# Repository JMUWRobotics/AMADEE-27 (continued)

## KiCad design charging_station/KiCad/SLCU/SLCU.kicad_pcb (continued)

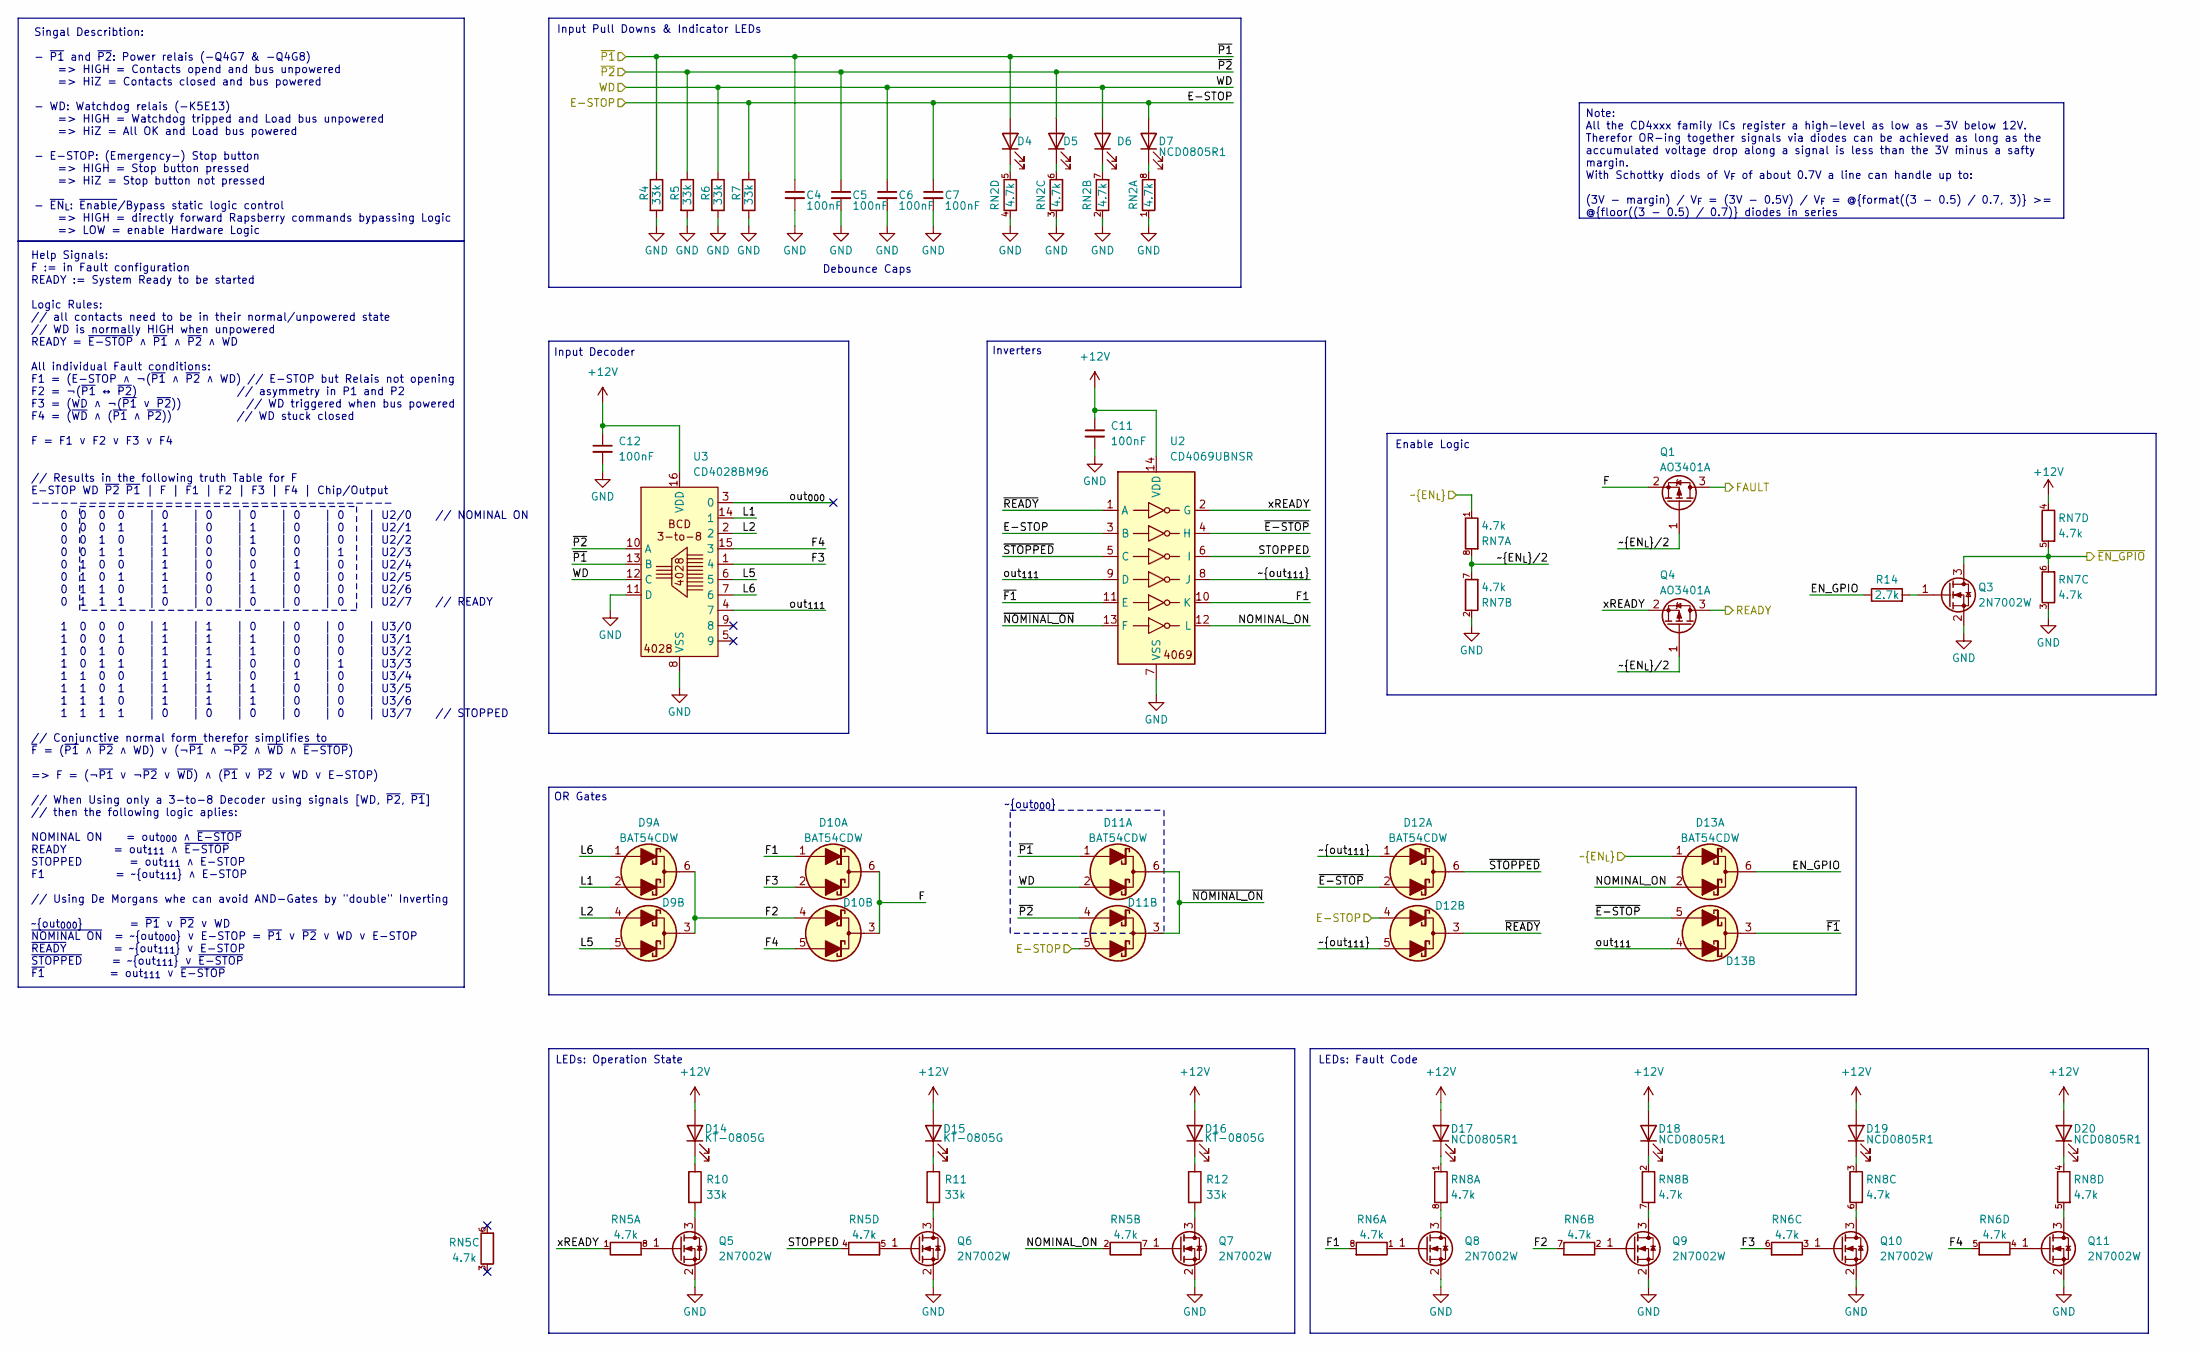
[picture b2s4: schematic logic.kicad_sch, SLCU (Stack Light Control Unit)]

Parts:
C4, C5, C6, C7, C11, C12: 100nF; C_0603_1608Metric
D4, D5, D6, D7, D17, D18, D19, D20: NCD0805R1; LED_0805_2012Metric_Pad1.15x1.40mm_HandSolder; MPN NCD0805R1; LCSC Part C84256
D9, D10, D11, D12, D13: BAT54CDW; SOT-363_SC-70-6
D14, D15, D16: KT-0805G; LED_0805_2012Metric_Pad1.15x1.40mm_HandSolder; MPN KT-0805G; LCSC Part C2297
Q1, Q4: AO3401A; SOT-23; MPN AO3401A; LCSC Part C15127
Q3, Q5, Q6, Q7, Q8, Q9, Q10, Q11: 2N7002W; SOT-323_SC-70; MPN 2N7002W; LCSC Part C7420322
R4, R5, R6, R7, R10, R11, R12: 33k; R_0402_1005Metric; LCSC Part C25779
R14: 2.7k; R_0603_1608Metric; LCSC Part C13167
RN2, RN5, RN6, RN7, RN8: 4.7k; RES-ARRAY-SMD_0603-8P-L3.2-W1.6-BL; MPN 4D03WGJ0472T5E; LCSC Part C1980
U2: CD4069UBNSR; SOIC127P780X200-14N; Mouser Part Number 595-CD4069UBNSR
U3: CD4028BM96; D16-L; MPN CD4028BM96; LCSC Part C131484

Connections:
+12V: C11.1, C12.1, D14.2 (A), D15.2 (A), D16.2 (A), D17.2 (A), D18.2 (A), D19.2 (A), D20.2 (A), RN7.4 (R4.1), U2.14 (VDD), U3.16 (VDD); also elsewhere on the board
/E-STOP: C7.1, D7.2 (A), D11.5 (A2), D12.4 (A2), R7.1, U2.3 (B); also elsewhere on the board
/Logic/EN_GPIO: D13.6 (K1), R14.1
/Logic/F: D10.3 (K2), D10.6 (K1), Q1.2 (S)
/Logic/F1: D10.1 (A1), RN6.8 (R1.2), U2.10 (K)
/Logic/F2: D9.3 (K2), D9.6 (K1), D10.4 (A2), RN6.7 (R2.2)
/Logic/F3: D10.2 (A1), RN6.6 (R3.2), U3.1 (4)
/Logic/F4: D10.5 (A2), RN6.5 (R4.2), U3.15 (3)
/Logic/FAULT: Q1.3 (D); also elsewhere on the board
/Logic/L1: D9.2 (A1), U3.14 (1)
/Logic/L2: D9.4 (A2), U3.2
/Logic/L5: D9.5 (A2), U3.6 (5)
/Logic/L6: D9.1 (A1), U3.7 (6)
/Logic/NOMINAL_ON: D13.2 (A1), RN5.2 (R2.1), U2.12 (L)
/Logic/READY: Q4.3 (D); also elsewhere on the board
/Logic/STOPPED: RN5.4 (R4.1), U2.6 (I)
/Logic/out_{000}: U3.3 (0)
/Logic/out_{111}: D13.4 (A2), U2.9 (D), U3.4 (7)
/Logic/xREADY: Q4.2 (S), RN5.1 (R1.1), U2.2 (G)
/Logic/~E-STOP: D12.2 (A1), D13.5 (A2), U2.4 (H)
/Logic/~EN_GPIO: Q3.3 (D), RN7.5 (R4.2), RN7.6 (R3.2); also elsewhere on the board
/Logic/~EN_{L}/2: Q1.1 (G), Q4.1 (G), RN7.7 (R2.2), RN7.8 (R1.2)
/Logic/~F1: D13.3 (K2), U2.11 (E)
/Logic/~NOMINAL_ON: D11.3 (K2), D11.6 (K1), U2.13 (F)
/Logic/~READY: D12.3 (K2), U2.1 (A)
/Logic/~STOPPED: D12.6 (K1), U2.5 (C)
/Logic/~out_{111}: D12.1 (A1), D12.5 (A2), U2.8 (J)
/WD: C6.1, D6.2 (A), D11.2 (A1), R6.1, U3.12 (C); also elsewhere on the board
/~EN_{L}: D13.1 (A1), RN7.1 (R1.1); also elsewhere on the board
/~P1: C4.1, D4.2 (A), D11.1 (A1), R4.1, U3.13 (B); also elsewhere on the board
/~P2: C5.1, D5.2 (A), D11.4 (A2), R5.1, U3.10 (A); also elsewhere on the board
GND: C4.2, C5.2, C6.2, C7.2, C11.2, C12.2, Q3.2 (S), Q5.2 (S), Q6.2 (S), Q7.2 (S), Q8.2 (S), Q9.2 (S), Q10.2 (S), Q11.2 (S), R4.2, R5.2, R6.2, R7.2, RN2.1 (R1.1), RN2.2 (R2.1), RN2.3 (R3.1), RN2.4 (R4.1), RN7.2 (R2.1), RN7.3 (R3.1), U2.7 (VSS), U3.8 (VSS), U3.11 (D); also elsewhere on the board
unnamed: D4.1 (K), RN2.5 (R4.2)
unnamed: D5.1 (K), RN2.6 (R3.2)
unnamed: D6.1 (K), RN2.7 (R2.2)
unnamed: D7.1 (K), RN2.8 (R1.2)
unnamed: D14.1 (K), R10.1
unnamed: D15.1 (K), R11.1
unnamed: D16.1 (K), R12.1
unnamed: D17.1 (K), RN8.1 (R1.1)
unnamed: D18.1 (K), RN8.2 (R2.1)
unnamed: D19.1 (K), RN8.3 (R3.1)
unnamed: D20.1 (K), RN8.4 (R4.1)
unnamed: Q3.1 (G), R14.2
unnamed: Q5.3 (D), R10.2
unnamed: Q5.1 (G), RN5.8 (R1.2)
unnamed: Q6.3 (D), R11.2
unnamed: Q6.1 (G), RN5.5 (R4.2)
unnamed: Q7.3 (D), R12.2
unnamed: Q7.1 (G), RN5.7 (R2.2)
unnamed: Q8.3 (D), RN8.8 (R1.2)
unnamed: Q8.1 (G), RN6.1 (R1.1)
unnamed: Q9.3 (D), RN8.7 (R2.2)
unnamed: Q9.1 (G), RN6.2 (R2.1)
unnamed: Q10.3 (D), RN8.6 (R3.2)
unnamed: Q10.1 (G), RN6.3 (R3.1)
unnamed: Q11.3 (D), RN8.5 (R4.2)
unnamed: Q11.1 (G), RN6.4 (R4.1)

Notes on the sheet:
Input Decoder
Enable Logic
~{out_{000}}
Help Signals: F := in Fault configuration READY := System Ready to be started Logic Rules: // all contacts need to be in their normal/unpowered state // WD is normally HIGH when unpowered READY = ~{E-STOP} ∧ ~{P1} ∧ ~{P2} ∧ WD All individual Fault conditions: F1 = (E-STOP ∧ ¬(~{P1} ∧ ~{P2} ∧ WD) //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
OR Gates
LEDs: Operation State
Singal Describtion: - ~{P1} and ~{P2}: Power relais (-Q4G7 & -Q4G8) => HIGH = Contacts opend and bus unpowered => HiZ = Contacts closed and bus powered - WD: Watchdog relais (-K5E13) => HIGH = Watchdog tripped and Load bus unpowered => HiZ = All OK and Load bus powered - E-STOP: (Emergency-) Stop b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
Debounce Caps
LEDs: Fault Code
Inverters
Input Pull Downs & Indicator LEDs
Note: All the CD4xxx family ICs register a high-level as low as -3V below 12V. Therefor OR-ing together signals via diodes can be achieved as long as the accumulated voltage drop along a signal is less than the 3V minus a safty margin. With Schottky diods of V_{F} of about 0.7V a line can handle up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

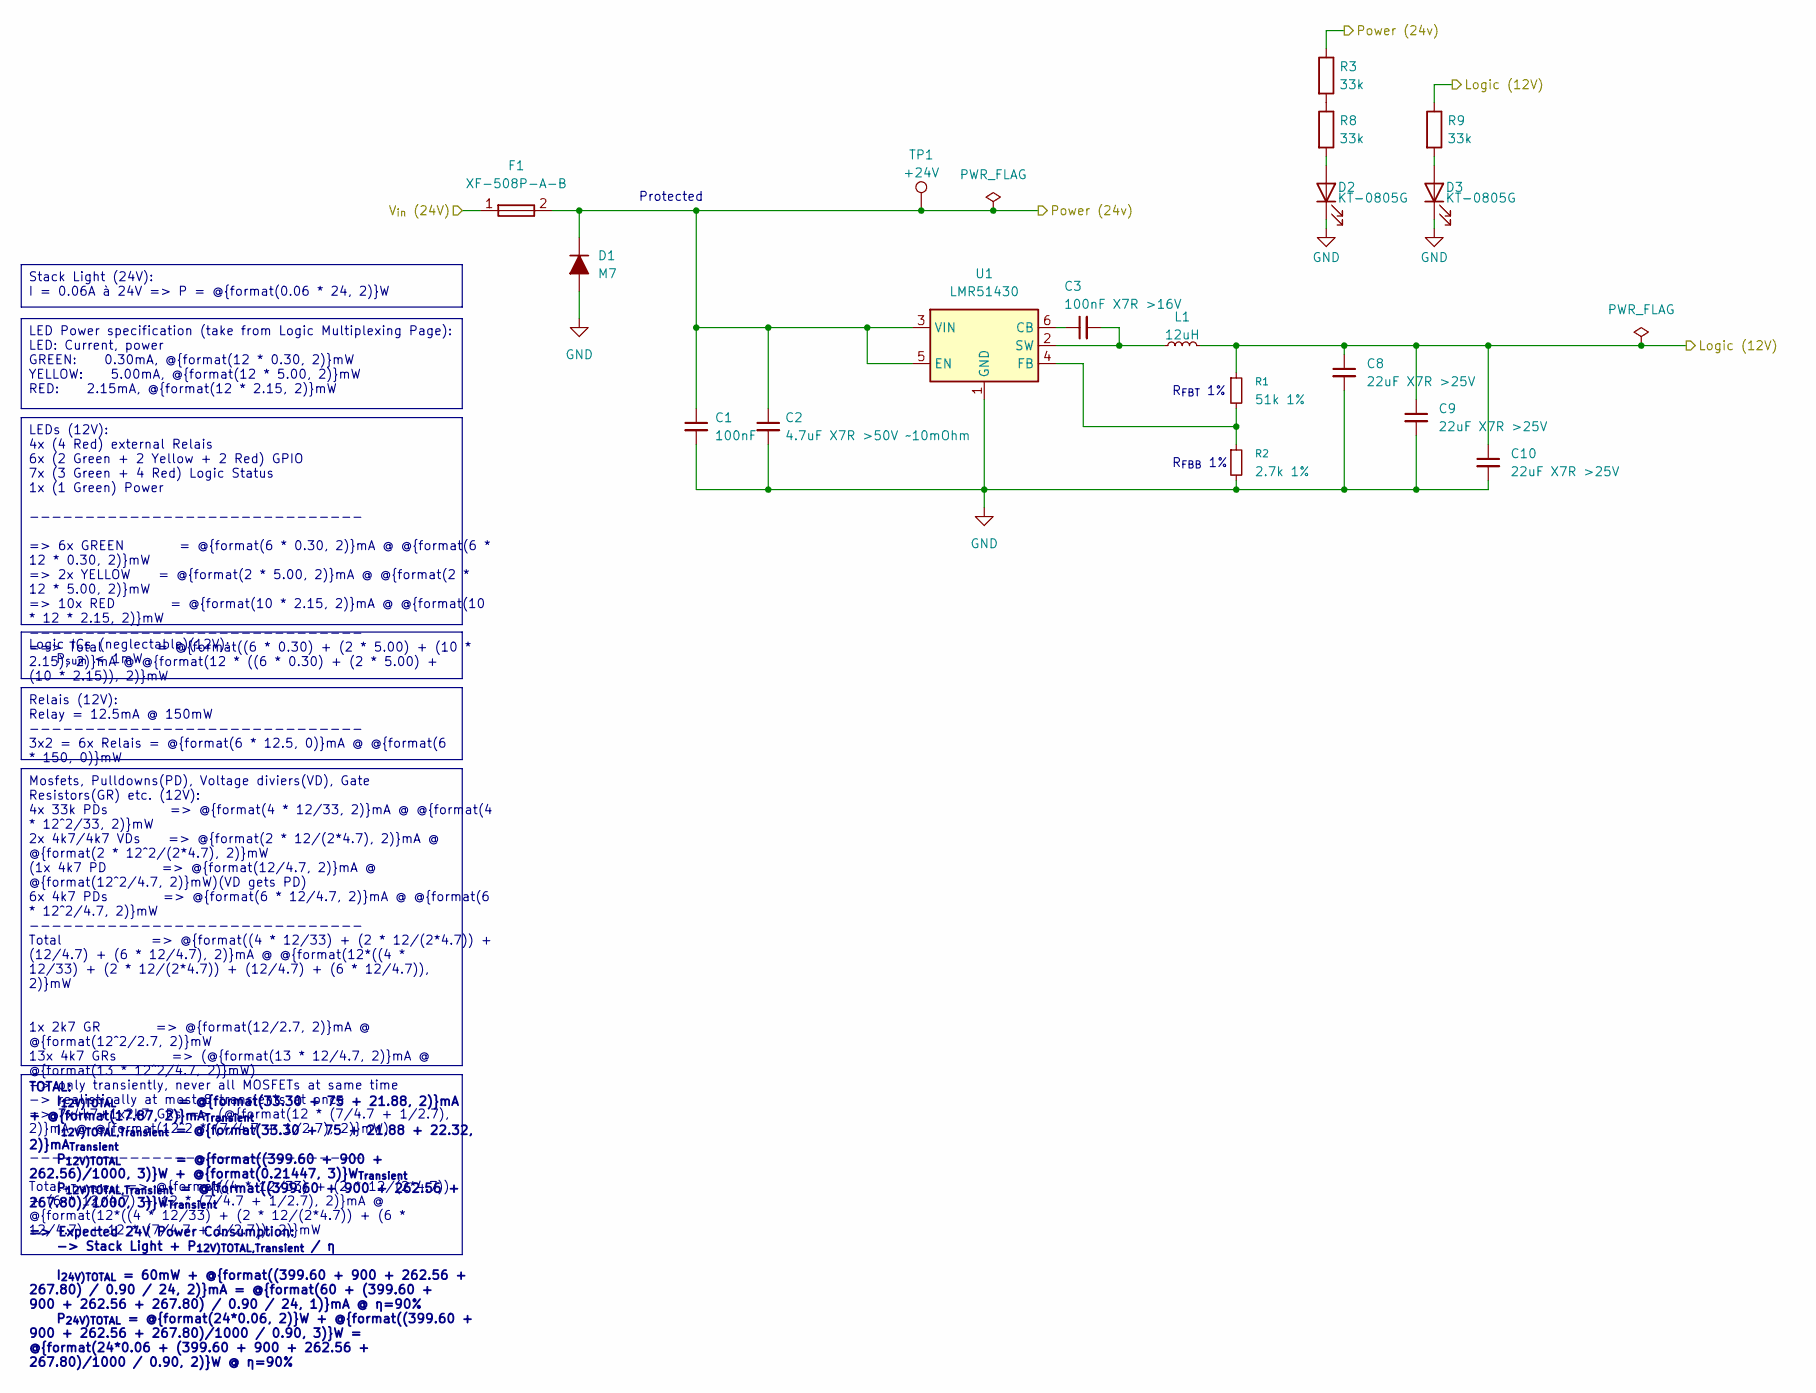
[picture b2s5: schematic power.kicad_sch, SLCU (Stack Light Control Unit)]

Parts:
C1: 100nF; C_0603_1608Metric
C2: 4.7uF X7R >50V ~10mOhm; C_1206_3216Metric
C3: 100nF X7R >16V; C_0603_1608Metric
C8, C9, C10: 22uF X7R >25V; C_0805_2012Metric_Pad1.18x1.45mm_HandSolder
D1: M7; D_SMA
D2, D3: KT-0805G; LED_0805_2012Metric_Pad1.15x1.40mm_HandSolder; MPN KT-0805G; LCSC Part C2297
F1: XF-508P-A-B; FUSE-TH_XF-508P-A-B; MPN XF-508P-A-B; LCSC Part C19727304
L1: 12uH; L_12x12mm_H8mm; MPN CDRH127NP-120MC; LCSC Part C338772
R1: 51k 1%; R_0603_1608Metric; LCSC Part C23196
R2: 2.7k 1%; R_0603_1608Metric; LCSC Part C13167
R3, R8, R9: 33k; R_0402_1005Metric; LCSC Part C25779
TP1: +24V; TestPoint_Pad_D1.5mm
U1: LMR51430; SOT-23-6

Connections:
+12V: C8.1, C9.1, C10.1, L1.2, R1.1, R9.1; also elsewhere on the board
+24V: C1.1, C2.1, D1.1 (K), F1.2, R3.1, TP1.1 (1_1), U1.3 (VIN), U1.5 (EN); also elsewhere on the board
/Power/V_{in} (24V): F1.1; also elsewhere on the board
GND: C1.2, C2.2, C8.2, C9.2, C10.2, D1.2 (A), D2.1 (K), D3.1 (K), R2.2, U1.1 (GND); also elsewhere on the board
unnamed: D2.2 (A), R8.2
unnamed: D3.2 (A), R9.2
unnamed: R3.2, R8.1
unnamed: C3.1, U1.6 (CB)
unnamed: R1.2, R2.1, U1.4 (FB)
unnamed: C3.2, L1.1, U1.2 (SW)

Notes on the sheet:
Protected
R_{FBT} 1%
R_{FBB} 1%
TOTAL: I_{12V)TOTAL} = @{format(33.30 + 75 + 21.88, 2)}mA + @{format(17.87, 2)}mA_{Transient} I_{12V)TOTAL,Transient} = @{format(33.30 + 75 + 21.88 + 22.32, 2)}mA_{Transient} P_{12V)TOTAL} = @{format((399.60 + 900 + 262.56)/1000, 3)}W + @{format(0.21447, 3)}W_{Transient} P_{12V)TOTAL,Transient} = @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
Relais (12V): Relay = 12.5mA @ 150mW ------------------------------ 3x2 = 6x Relais = @{format(6 * 12.5, 0)}mA @ @{format(6 * 150, 0)}mW
Stack Light (24V): I = 0.06A à 24V => P = @{format(0.06 * 24, 2)}W
Logic ICs (neglectable)(12V): P_{sum} < 1mW
LEDs (12V): 4x (4 Red) external Relais 6x (2 Green + 2 Yellow + 2 Red) GPIO 7x (3 Green + 4 Red) Logic Status 1x (1 Green) Power ------------------------------ => 6x GREEN = @{format(6 * 0.30, 2)}mA @ @{format(6 * 12 * 0.30, 2)}mW => 2x YELLOW = @{format(2 * 5.00, 2)}mA @ @{format(2 * 12 * 5.00, 2)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
Mosfets, Pulldowns(PD), Voltage diviers(VD), Gate Resistors(GR) etc. (12V): 4x 33k PDs => @{format(4 * 12/33, 2)}mA @ @{format(4 * 12^2/33, 2)}mW 2x 4k7/4k7 VDs => @{format(2 * 12/(2*4.7), 2)}mA @ @{format(2 * 12^2/(2*4.7), 2)}mW (1x 4k7 PD => @{format(12/4.7, 2)}mA @ @{format(12^2/4.7, 2)}mW)(VD g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
LED Power specification (take from Logic Multiplexing Page): LED: Current, power GREEN: 0.30mA, @{format(12 * 0.30, 2)}mW YELLOW: 5.00mA, @{format(12 * 5.00, 2)}mW RED: 2.15mA, @{format(12 * 2.15, 2)}mW

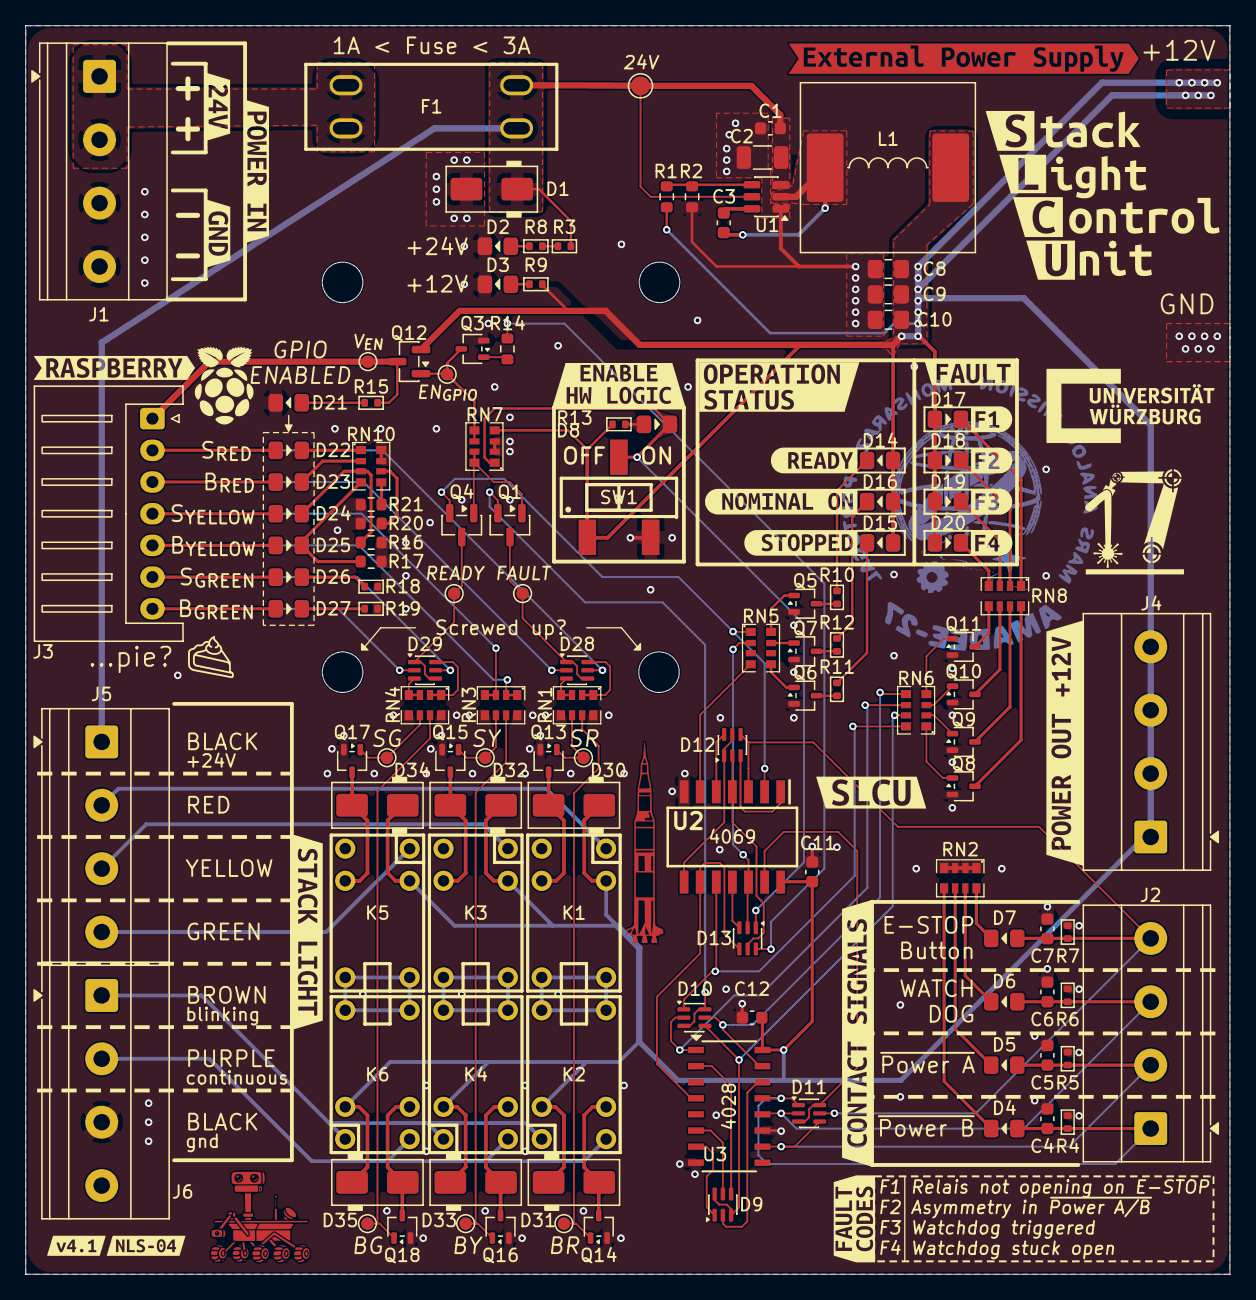
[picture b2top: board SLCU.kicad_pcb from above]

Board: 2 copper layers, 95.0 x 98.5 mm, 160 parts (0 on the bottom side), 106 nets.

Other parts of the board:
kibuzzard-6ACFD63A: G***; kibuzzard-6ACFD63A
kibuzzard-6ACFD560: G***; kibuzzard-6ACFD560
kibuzzard-6ACFDAEA: G***; kibuzzard-6ACFDAEA
kibuzzard-6ACFDB30: G***; kibuzzard-6ACFDB30
kibuzzard-6ACFDB37: G***; kibuzzard-6ACFDB37
kibuzzard-6ACFDC5F: G***; kibuzzard-6ACFDC5F
kibuzzard-6ACFDC7C: G***; kibuzzard-6ACFDC7C
kibuzzard-6ACFDC65: G***; kibuzzard-6ACFDC65
kibuzzard-6ACFDC83: G***; kibuzzard-6ACFDC83
kibuzzard-6ACFDD22: G***; kibuzzard-6ACFDD22
kibuzzard-6ACFDD51: G***; kibuzzard-6ACFDD51
kibuzzard-6ACFDDC7: G***; kibuzzard-6ACFDDC7
kibuzzard-6ACFDE5B: G***; kibuzzard-6ACFDE5B
kibuzzard-6ACFDF9B: G***; kibuzzard-6ACFDF9B
kibuzzard-6ACFDF9F: G***; kibuzzard-6ACFDF9F
kibuzzard-6ACFDF95: G***; kibuzzard-6ACFDF95
kibuzzard-6ACFDFA3: G***; kibuzzard-6ACFDFA3
kibuzzard-6ACFDFAE: G***; kibuzzard-6ACFDFAE
kibuzzard-6ACFDFB1: G***; kibuzzard-6ACFDFB1
kibuzzard-6ACFDFBD: G***; kibuzzard-6ACFDFBD
kibuzzard-6ACFDFF0: G***; kibuzzard-6ACFDFF0
kibuzzard-6ACFE1C2: G***; kibuzzard-6ACFE1C2
kibuzzard-6ACFE19D: G***; kibuzzard-6ACFE19D
kibuzzard-6ACFE193: G***; kibuzzard-6ACFE193
kibuzzard-6AD01D0B: G***; kibuzzard-6AD01D0B
kibuzzard-6AD0072F: G***; kibuzzard-6AD0072F
kibuzzard-6AD0073C: G***; kibuzzard-6AD0073C
kibuzzard-6AD00824: G***; kibuzzard-6AD00824
kibuzzard-6AFE16E9: G***; kibuzzard-6AFE16E9
kibuzzard-6B007FCD: G***; kibuzzard-6B007FCD
kibuzzard-6B0316A7: G***; kibuzzard-6B0316A7

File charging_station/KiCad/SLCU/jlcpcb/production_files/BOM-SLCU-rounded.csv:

Comment,Designator,Footprint,LCSC,Quantity
100nF,"C1,C11,C12,C4,C5,C6,C7",C_0603_1608Metric,C14663,7
100nF X7R >16V,C3,C_0603_1608Metric,C14663,1
12uH,L1,L_12x12mm_H8mm,C338772,1
2.7k,"R14,R16,R17,R20,R21",R_0603_1608Metric,C13167,5
2.7k 1%,R2,R_0603_1608Metric,C13167,1
22uF X7R >25V,"C10,C8,C9",C_0805_2012Metric_Pad1.18x1.45mm_HandSolder,C45783,3
2N7002W,"Q10,Q11,Q13,Q14,Q15,Q16,Q17,Q18,Q3,Q5,Q6,Q7,Q8,Q9",SOT-323_SC-70,C7420322,14
33k,"R10,R11,R12,R13,R15,R18,R19,R3,R4,R5,R6,R7,R8,R9",R_0402_1005Metric,C25779,14
4.7k,"RN1,RN10,RN2,RN3,RN4,RN5,RN6,RN7,RN8",RES-ARRAY-SMD_0603-8P-L3.2-W1.6-BL,C20197,9
4.7uF X7R >50V ~10mOhm,C2,C_1206_3216Metric,C29823,1
51k 1%,R1,R_0603_1608Metric,C23196,1
AO3401A,"Q1,Q12,Q4",SOT-23,C15127,3
BAT54CDW,"D10,D11,D12,D13,D28,D29,D9",SOT-363_SC-70-6,C49190672,7
CD4028BM96,U3,D16-L,C131484,1
CD4069UBNSR,U2,SOIC127P780X200-14N,C2866535,1
Contact Signals,J2,"TerminalBlock_Phoenix_MKDS-1,5-4_1x04_P5.00mm_Horizontal",C3817931,1
Enable Logic,SW1,SW-SMD_SHOUHAN_MST-22D18G23J_C2875122,C2875122,1
HRB1-S-DC12V,"K1,K2,K3,K4,K5,K6",RELAY-TH_HRB1-S-X,C125705,6
Input Power (24V),J1,"TerminalBlock_Phoenix_MKDS-1,5-4_1x04_P5.00mm_Horizontal",C3817931,1
KT-0805G,"D14,D15,D16,D2,D21,D26,D27,D3,D8",LED_0805_2012Metric_Pad1.15x1.40mm_HandSolder,C2297,9
KT-0805Y,"D24,D25",LED_0805_2012Metric_Pad1.15x1.40mm_HandSolder,C2296,2
LMR51430,U1,SOT-23-6,C5185863,1
Logic Power Out,J4,"TerminalBlock_Phoenix_MKDS-1,5-4_1x04_P5.00mm_Horizontal",C3817931,1
M7,"D1,D30,D31,D32,D33,D34,D35",D_SMA,C95872,7
NCD0805R1,"D17,D18,D19,D20,D22,D23,D4,D5,D6,D7",LED_0805_2012Metric_Pad1.15x1.40mm_HandSolder,C84256,10
Raspberry Control Signals,J3,JST_XH_S7B-XH-A_1x07_P2.50mm_Horizontal,C157916,1
Stack Light DOWN,J6,"TerminalBlock_Phoenix_MKDS-1,5-4_1x04_P5.00mm_Horizontal",C3817931,1
Stack Light UP,J5,"TerminalBlock_Phoenix_MKDS-1,5-4_1x04_P5.00mm_Horizontal",C3817931,1
XF-508P-A-B,F1,FUSE-TH_XF-508P-A-B,C19727304,1

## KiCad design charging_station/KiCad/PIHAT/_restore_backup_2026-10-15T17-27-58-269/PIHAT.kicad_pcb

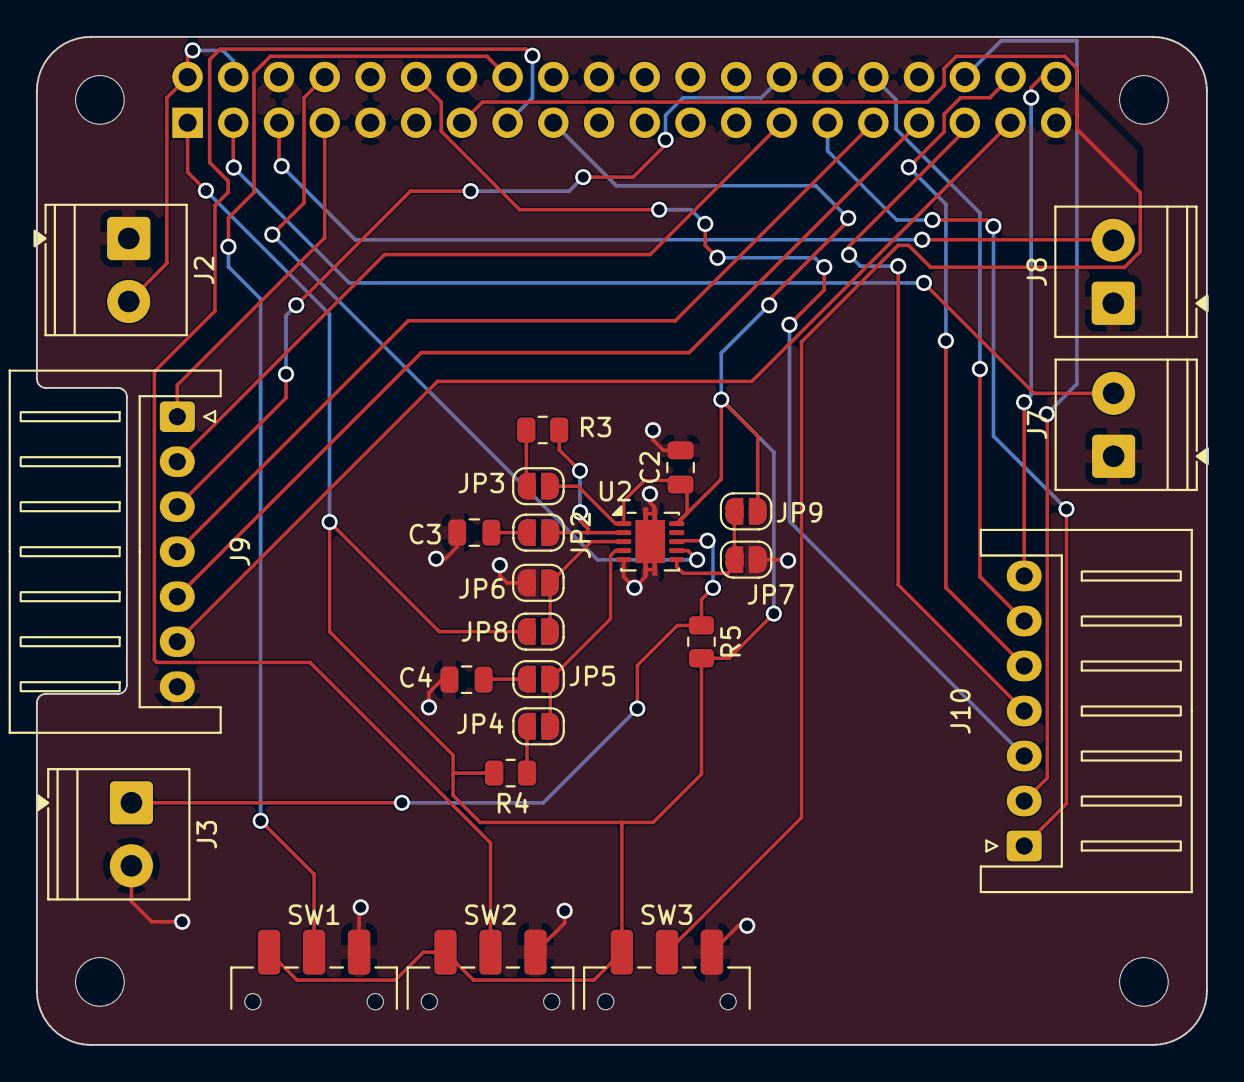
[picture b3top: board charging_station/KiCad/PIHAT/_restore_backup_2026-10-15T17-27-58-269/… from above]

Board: 2 copper layers, 65.0 x 56.0 mm, 29 parts (1 on the bottom side), 31 nets.

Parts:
C2: 100nf; C_0805_2012Metric
C3, C4: C; C_0805_2012Metric
J1: GPIO; PinSocket_2x20_P2.54mm_Vertical
J2: 5v(Vin); TerminalBlock_Phoenix_PT-1,5-2-3.5-H_1x02_P3.50mm_Horizontal
J3: WD_F; TerminalBlock_Phoenix_PT-1,5-2-3.5-H_1x02_P3.50mm_Horizontal
J7: MPPT; TerminalBlock_Phoenix_PT-1,5-2-3.5-H_1x02_P3.50mm_Horizontal
J8: PS; TerminalBlock_Phoenix_PT-1,5-2-3.5-H_1x02_P3.50mm_Horizontal
J9: Stack light; JST_XH_S7B-XH-A_1x07_P2.50mm_Horizontal
J10: RFID; JST_XH_S7B-XH-A_1x07_P2.50mm_Horizontal
JP2, JP3, JP4, JP5, JP6, JP7, JP8, JP9: SolderJumper_2_Open; SolderJumper-2_P1.3mm_Open_RoundedPad1.0x1.5mm
MH1, MH2, MH3, MH4: MountingHole_2.7mm_M2.5
R3, R5: 10k; R_0805_2012Metric
R4: R; R_0805_2012Metric
SW1, SW2, SW3: Sw_1; SW_SPDT_CK_JS102011SAQN
U2: TPS3430WDRC; VSON-10-1EP_3x3mm_P0.5mm_EP1.65x2.4mm

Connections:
/Raspi5/3v3: C2.1, J1.1, J1.17, JP3.1 (A), JP8.2 (B), JP9.2 (B), R4.1, R5.2, SW1.1, SW2.1, SW3.1, U2.1 (VDD1), U2.10 (VDD2)
/Raspi5/5v: J1.2, J1.4, J2.2
/Raspi5/GPIO0/R_MO: J1.27, J9.2
/Raspi5/GPIO1/Y_ST: J1.28, J9.3
/Raspi5/GPIO2/MPPT: J1.3, J7.2
/Raspi5/GPIO3/PS: J1.5, J8.2
/Raspi5/GPIO4/R_ST: J1.7, J9.1
/Raspi5/GPIO5/CE1: J1.29, J10.1
/Raspi5/GPIO6/Y_MO: J1.31, J9.4
/Raspi5/GPIO12/RST: J1.32, J10.6
/Raspi5/GPIO13/G_ST: J1.33, J9.5
/Raspi5/GPIO14/GPIO_WD: J1.8, U2.7 (WDI)
/Raspi5/GPIO16/CE2: J1.36, J10.2
/Raspi5/GPIO18/CE0: J1.12, J10.3
/Raspi5/GPIO19/MISO: J1.35, J10.4
/Raspi5/GPIO20/MOSI: J1.38, J10.5
/Raspi5/GPIO21/CLK: J1.40, J10.7
/Raspi5/GPIO22: J1.15, SW2.2 (3)
/Raspi5/GPIO23: J1.16, SW1.2 (3)
/Raspi5/GPIO26/G_MO: J1.37, J9.6
/Raspi5/GPIO27: J1.13, SW3.2 (3)
/Watchdog/WD_FAULT: J3.1, R5.1, U2.8 (~WDO)
GND: C2.2, C3.1, C4.1, J1.6, J1.9, J1.14, J1.20, J1.25, J1.30, J1.34, J1.39, J2.1, J3.2, J7.1, J8.1, J9.7, JP6.1 (A), JP7.1 (A), SW1.3 (4), SW2.3 (4), SW3.3 (4), U2.5 (GND), U2.11 (GND)
unnamed: C3.2, JP2.1 (A)
unnamed: JP2.2 (B), R3.1, U2.2 (CWD)
unnamed: JP3.2 (B), R3.2
unnamed: JP4.1 (A), JP5.2 (B), U2.4 (CRST)
unnamed: JP4.2 (B), R4.2
unnamed: C4.2, JP5.1 (A)
unnamed: JP6.2 (B), JP8.1 (A), U2.3 (SET0)
unnamed: JP7.2 (B), JP9.1 (A), U2.6 (SET1)

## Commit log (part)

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2026-04-27 init readme
2026-04-27 license init
    MIT ? double check later
2026-06-23 charging station: add initial dpm86 api
2026-06-23 charging station: updated ansi coloring
2026-06-23 charging station: move api
2026-06-23 charging station: simple test
